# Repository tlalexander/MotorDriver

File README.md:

# MotorDriver

This is a smart brushless motor driver board capable of precision servo-control (position and velocity control) of a low cost hobby brushless motor. This is managed by use of a magnetic angle sensor, and a feedback software that runs on the motor driver's onboard 64MHz ARM CPU.

The board is still under development, but the ultimate goal of this board is to enable lower cost robotics, especially for hobbyists.

Brushless motors have excellent torque characteristics, but complexity in their control has meant that complex gear reductions are typically needed to make use of these motors. With improved precision on motion control, larger motors can be used in lieu of complex gear trains, reducing system complexity.

Essentially, this board moves a mechanical problem to a software problem.

This is specifically quite helpful in the field of ultra low cost 3D printed robotics, where simpler mechanisms enable near zero cost robots to be built at home.

This board is designed to facilitate the development of these applications, but is not itself particularly low cost. If you like the idea of good quality brushless motor control for hobbyist robotics, please fork this project, simplify the design, and flood the market with cheap clones from China.

### Note 7/8/2016:
The current board design works with some changes. I haven't published the changes yet. If you want to make one, contact me first. I'd be happy to push the changes if someone wants to make some of these.

Features (planned)
------

* At least 1kW maximum power handling (depending on FETs used; theoretical max power for this FET package is 3kW).
* Current feedback for proper current-based motor control.
* Position feedback via external magentic encoder enables full closed loop control of low cost hobby brushless motors.
* Devices can be synchronized for six wire motor control (custom windings, linear motors, etc).
* Independent control of all bridges allows for brushed motor control with an additional half H bridge for other loads.
* USB interface allows easy control from a linux PC. Serial interface allows control from embedded systems such as Arduino.
* CPU runs Arduino code for easy portability.
* Multicolor LED to indicate status.

TODO
-----

* ~~Determine necessary device pinout and add properly wired headers.~~
* ~~Finish layout of current sense section.~~
* ~~Add jumper for battery power to CPU.~~
* ~~Full design review (is everything hooked up right?).~~
* ~~Finish all layout of Board V1.~~
* ~~Produce first test version.~~
* Full board test. (in progress)
* Write firmware for device.

Media
-----
It works! Check out the sweet video:
https://www.youtube.com/watch?v=cGBqlPRFbaQ

License
-----

This project is licensed under Creative Commons Attribution-ShareAlike 4.0 International (CC BY-SA 4.0), which is available at: http://creativecommons.org/licenses/by-sa/4.0/ If you use the files, please check them carefully - they may contain errors.

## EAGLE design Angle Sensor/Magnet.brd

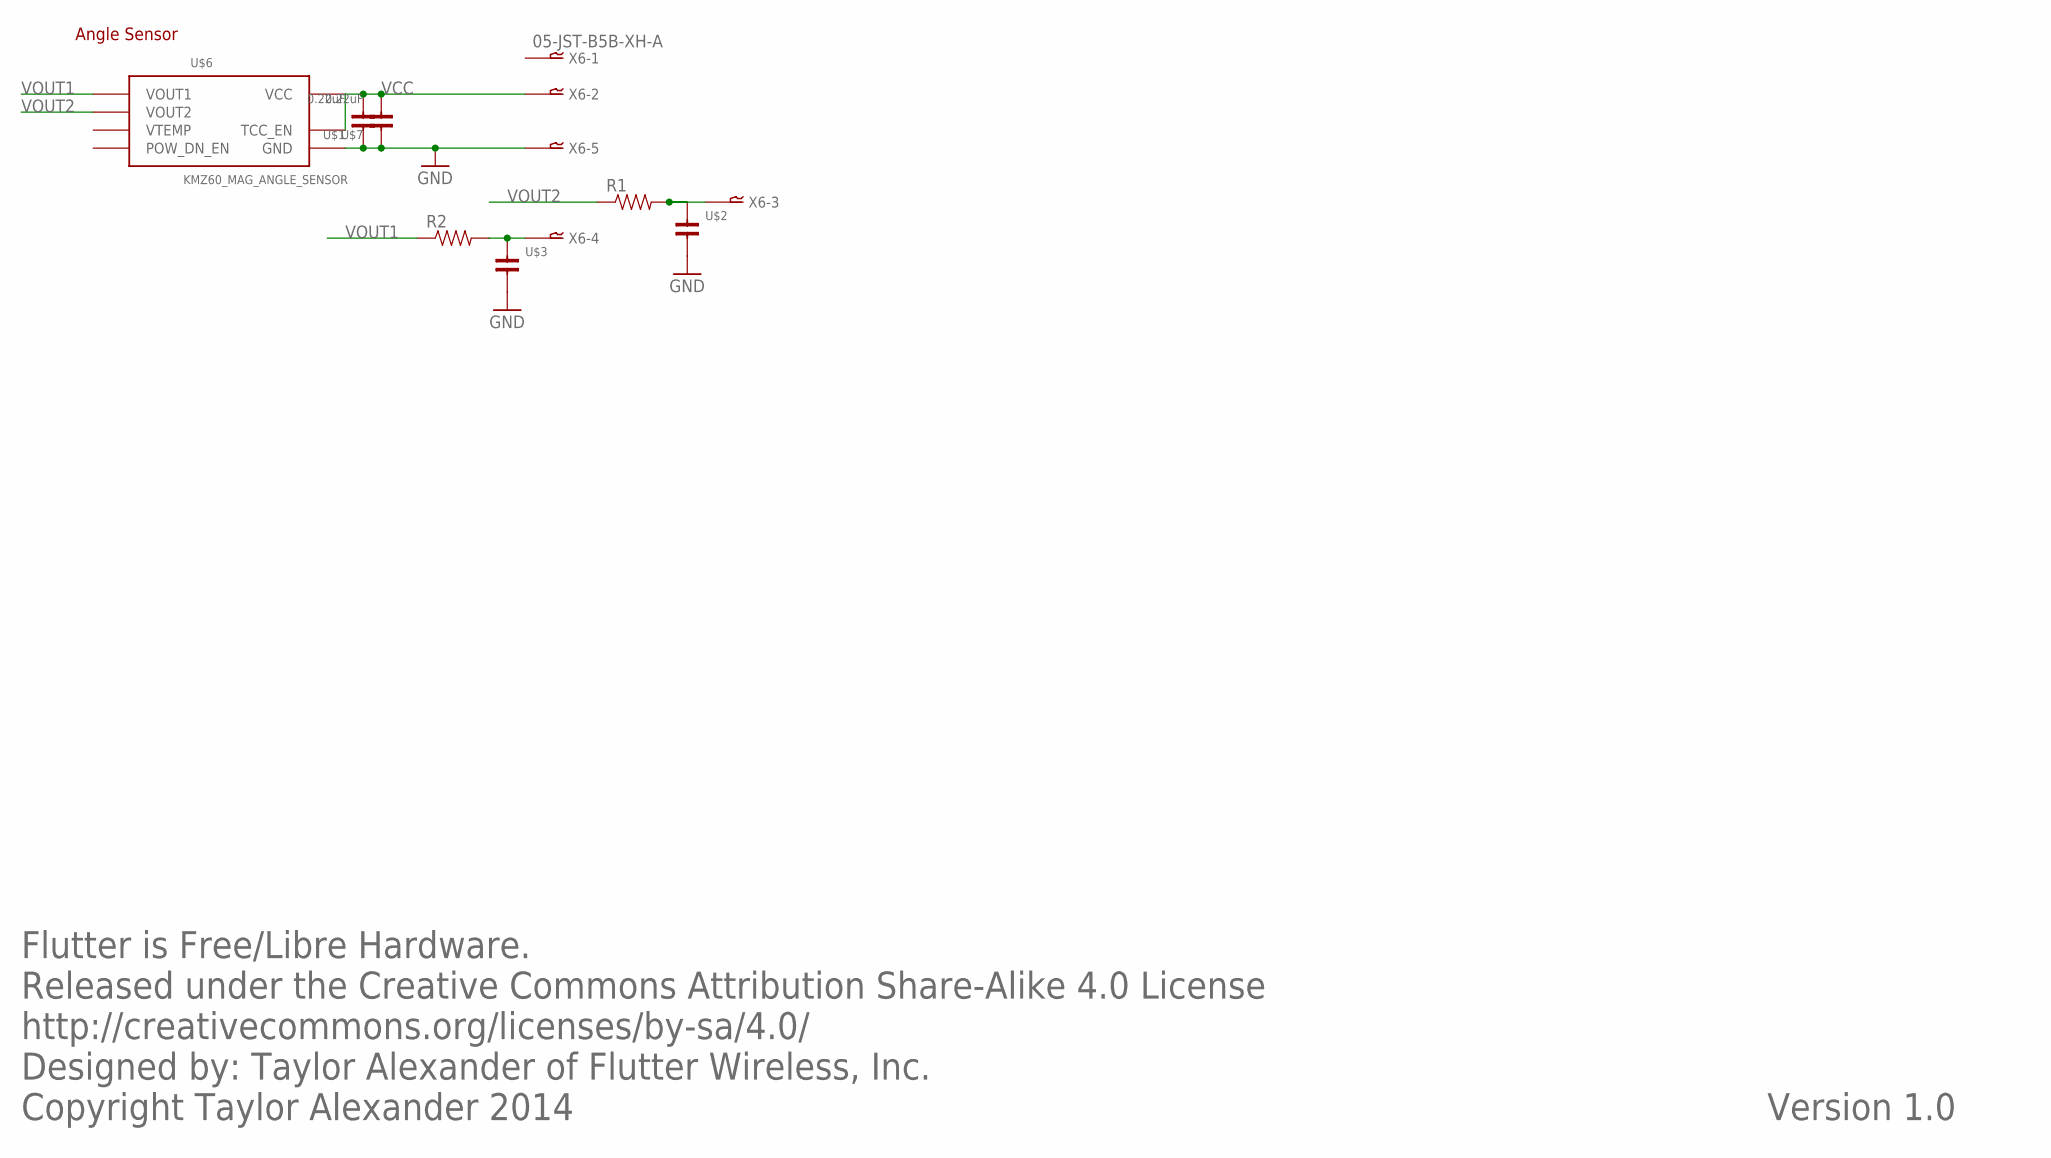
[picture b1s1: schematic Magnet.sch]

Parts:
R1, R2: RESISTOR0603; 0603-RES
U$1, U$7: 0.22uF; 0808-CAP
U$2, U$3: CAPACITOR0603-CAP; 0603-CAP
U$6: KMZ60_MAG_ANGLE_SENSOR; SO-8
X6: 05-JST-B5B-XH-A; B5B-XH

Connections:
GND: U$1.1, U$2.2, U$3.2, U$6.P$3 (GND), U$6.P$6 (GND), U$7.1, X6.P$5
unnamed: R2.2, U$3.1, X6.P$4
unnamed: R1.2, U$2.1, X6.P$3
VCC: U$1.2, U$6.P$1 (TCC_EN), U$6.P$7 (VCC), U$7.2, X6.P$2
VOUT1: R2.1, U$6.P$2 (VOUT1)
VOUT2: R1.1, U$6.P$4 (VOUT2)

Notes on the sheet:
Flutter is Free/Libre Hardware. Released under the Creative Commons Attribution Share-Alike 4.0 License http://creativecommons.org/licenses/by-sa/4.0/ Designed by: Taylor Alexander of Flutter Wireless, Inc. Copyright Taylor Alexander 2014
Version 1.0
Angle Sensor

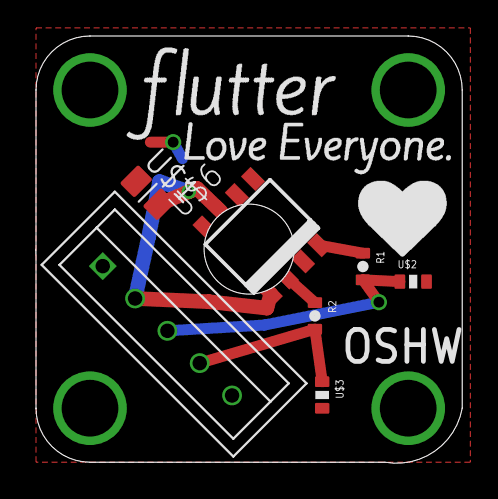
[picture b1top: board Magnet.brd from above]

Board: 2 copper layers, 23.7 x 23.7 mm, 8 parts (1 on the bottom side), 6 nets.

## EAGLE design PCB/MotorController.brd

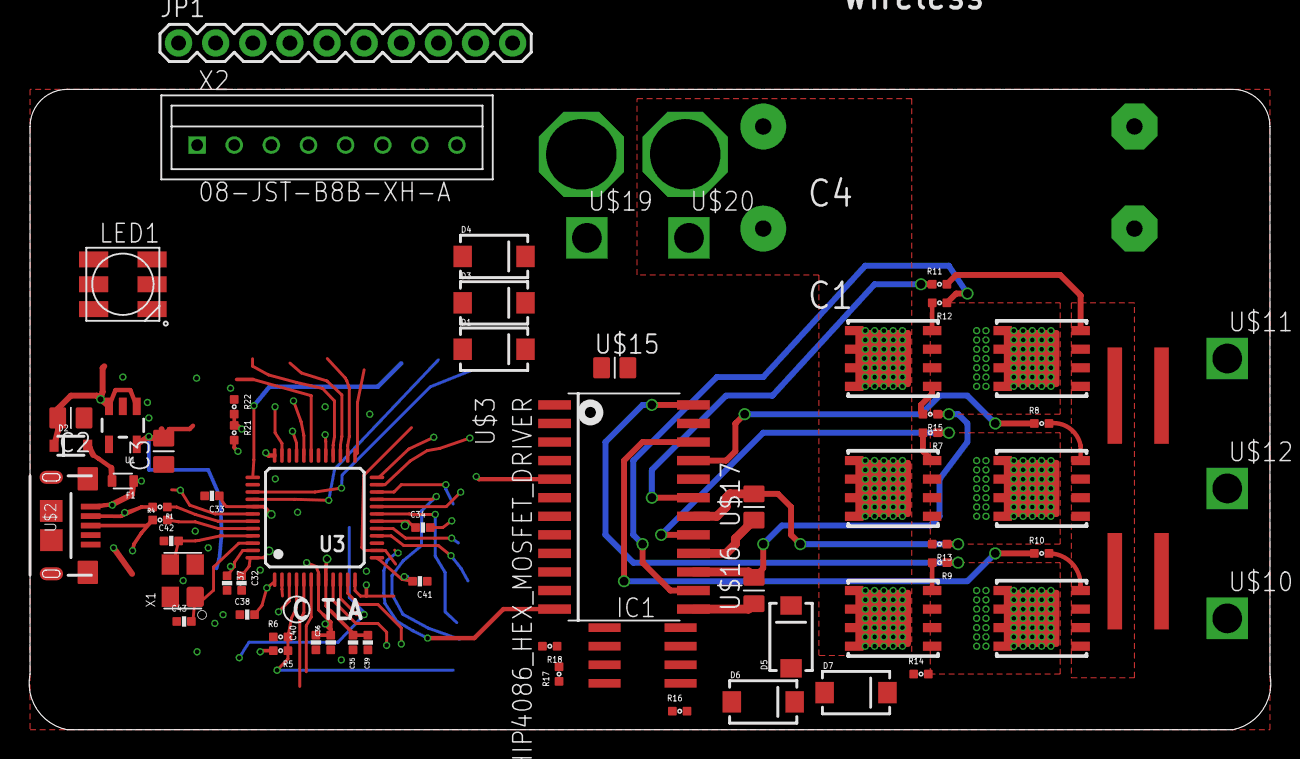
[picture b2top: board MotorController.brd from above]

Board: 4 copper layers, 84.9 x 43.8 mm, 69 parts (0 on the bottom side), 47 nets.

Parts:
C1, C4: CAP-6.5X18MM
C2, C3: 4.7uF 35v 490-7208-1-ND; 0808-CAP
C32, C33, C34, C35, C36, C37, C38, C41: 0.1uF; 0402-CAP
C39, C40: 2.2uF; 0402-CAP
C42, C43: 15pF; 0402-CAP
D1, D3, D4, D5, D6, D7: SMA-DIODE
D2: SOD-323
F1: 500mA; 0603-PTC
IC1: OPA333D; SO08
JP1: M10"; 1X10
LED1: WS2812
R1, R4: 27R; 0402-RES
R2, R3: OHMITE_FCSL64_CURRENT_SENSE_RESISTOR
R5: 6.49k; 0402-RES
R6, R21: 1k; 0402-RES
R7, R8, R9, R10, R11, R12: 33; 0402-RES
R13, R14, R15, R16, R17, R18: 4.7; 0402-RES
R22: 2k; 0402-RES
U1: MIC5235-3.3; SOT23-5
U3: SAM3S4/2/1A_48PIN_LQFP; LQFP48
U$1: OSHW-LOGOS; OSHW-LOGO-S
U$2: MICRO_USB; MICRO-USB-SLOT-2
U$3: HIP4086_HEX_MOSFET_DRIVER; SOIC-24
U$4, U$5, U$6, U$7, U$8, U$9: MOSFETSO-8; POWERPAK_S0-8
U$10, U$11, U$12, U$19, U$20: HIGHCURRENTPAD2; HIGH_CURRENT_PAD2
U$15, U$16, U$17: 0.22uF; 0808-CAP
U$21: XT60; XT60_CONNECTOR
X1: 12MHz; XTAL_ABRACON_ABM8G_3.2MMX2.5MM
X2: 08-JST-B8B-XH-A; B8B-XH

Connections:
3.3V: C3.2, C36.2, C37.1, C38.2, C40.1, C41.2, U1.5, U3.1, U3.7, U3.13, U3.33, U3.47
+1.8V: C32.1, C33.1, C34.1, C35.1, C39.1, U3.8, U3.18, U3.41, U3.48
+3V3: IC1.7, LED1.LEDVDD, LED1.VDD
A: R15.2, U$6.S@1, U$6.S@2, U$6.S@3, U$9.D@1, U$9.D@2, U$9.D@3, U$9.D@4, U$9.DTOP, U$11.P$1
A2: IC1.6, R16.2, R17.1, U3.9
A3/PWML0: U3.11, U$3.P$4
AHO: R7.1, U$3.P$17
AHS: D6.C, R13.1, U$3.P$18, U$17.2
ALO: R8.1, U$3.P$21
B: R13.2, U$4.S@1, U$4.S@2, U$4.S@3, U$7.D@1, U$7.D@2, U$7.D@3, U$7.D@4, U$7.DTOP, U$12.P$1
BHO: R9.1, U$3.P$24
BHS: D7.C, R14.1, U$3.P$23, U$15.2
BLO: R10.1, U$3.P$22
C: R14.2, U$5.S@1, U$5.S@2, U$5.S@3, U$8.D@1, U$8.D@2, U$8.D@3, U$8.D@4, U$8.DTOP, U$10.P$1
CHO: R12.1, U$3.P$14
CHS: D5.C, R15.1, U$3.P$15, U$16.2
CLO: R11.1, U$3.P$19
D8/PWMH1: U3.35, U$3.P$2
D9/PWMH2: U3.32, U$3.P$12
GND: C1.-, C2.1, C3.1, C4.-, C32.2, C33.2, C34.2, C35.2, C36.1, C37.2, C38.1, C39.2, C40.2, C41.1, C42.1, C43.1, D5.A, D6.A, D7.A, IC1.4, LED1.VSS, R2.P$1, R3.P$1, R6.1, R16.1, R18.2, R22.1, U1.2, U3.2, U3.30, U3.34, U3.38, U$2.GND, U$2.PAD1, U$2.PAD2, U$2.PAD3, U$2.PAD4, U$2.PAD5, U$2.PAD6, U$2.PAD7, U$2.PAD8, U$3.P$6, U$19.P$1, U$21.P$2, X1.P$2, X1.P$4
unnamed: D3.C, U$3.P$16, U$17.1
unnamed: D1.A, D3.A, D4.A
unnamed: IC1.2, R17.2, R18.1
unnamed: R7.2, U$4.G
unnamed: R8.2, U$7.G
unnamed: D2.2, F1.2
unnamed: R9.2, U$5.G
unnamed: R10.2, U$8.G
unnamed: R11.2, U$9.G
unnamed: R12.2, U$6.G
unnamed: D1.C, U$3.P$1, U$15.1
unnamed: D4.C, U$3.P$13, U$16.1
unnamed: C42.2, U3.45, X1.P$3
unnamed: C43.2, U3.46, X1.P$1
RAW: C2.2, D2.1, R5.2, U1.1, U1.3
S0/UVCCDIV: R21.1, R22.2, U3.23
S1/PWML1: U3.12, U$3.P$3
S2/PWMH0: LED1.DI, U3.36, U$3.P$5
S3/PWML2: U3.14, U$3.P$11
S11/A5: R5.1, R6.2, U3.4
UDDC_+: R4.2, U3.44
UDDC_-: R1.2, U3.43
UDDM: R1.1, U$2.D-
UDDP: R4.1, U$2.D+
UVCC: F1.1, R21.2, U$2.VBUS
VMOT: C1.+, C4.+, U$4.D@1, U$4.D@2, U$4.D@3, U$4.D@4, U$4.DTOP, U$5.D@1, U$5.D@2, U$5.D@3, U$5.D@4, U$5.DTOP, U$6.D@1, U$6.D@2, U$6.D@3, U$6.D@4, U$6.DTOP, U$20.P$1, U$21.P$1
VSENSE: IC1.3, R2.P$2, R3.P$2, U$7.S@1, U$7.S@2, U$7.S@3, U$8.S@1, U$8.S@2, U$8.S@3, U$9.S@1, U$9.S@2, U$9.S@3

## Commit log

2016-01-04 Updated License
2016-01-04 Added description to Readme
2016-01-04 Added call to arms
2016-01-04 Added bullets to list
2016-01-04 Added TODO
2016-01-04 Move current sense circuit around, update readme
2016-03-01 Added 12v power supply, removed CPU in favor of Flutter (for quick development), added headers... many other changes. This commit represents version 0.1 of the hardware.
2016-04-13 Added BOM, Added PDFs of Schematic and PCB, Updated Project Status in Readme, added video to Readme
2016-08-08 Updated readme. Also pushing latest changes to board. Can't actually remember what they are.
2016-08-08 Updated Readme. Added today's date to note.
2016-09-05 Updated wiring for better compatibility with Flutter, fixed current sense filter, removed angle sensor.
2017-02-16 Added angle sensor. Checked in latest board version.
